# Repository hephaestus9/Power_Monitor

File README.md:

Power_Monitor
=============

Arduino and Processing sketches for Power Monitor Shield

*Boards v1r3 and v2r1 are not fully tested

This project is based on the work done by Christopher McNally.
Please view the Design_Report.pdf document for the write up of the project, and [website] (http://people.ece.cornell.edu/land/courses/eceprojectsland/STUDENTPROJ/2009to2010/csm44/index.html).

>The sample code was written for use with the 3000 Turn [CR Magnetics](http://www.crmagnetics.com/Products/CR3100-Series-P75.aspx) split core transformer. 

>If using the current transformer from [seeedstudio](http://www.seeedstudio.com/depot/Noninvasive-AC-Current-Sensor-100A-max-p-547.html?cPath=25_28) then the code needs to be changed, as this is a 2000 turn transformer.

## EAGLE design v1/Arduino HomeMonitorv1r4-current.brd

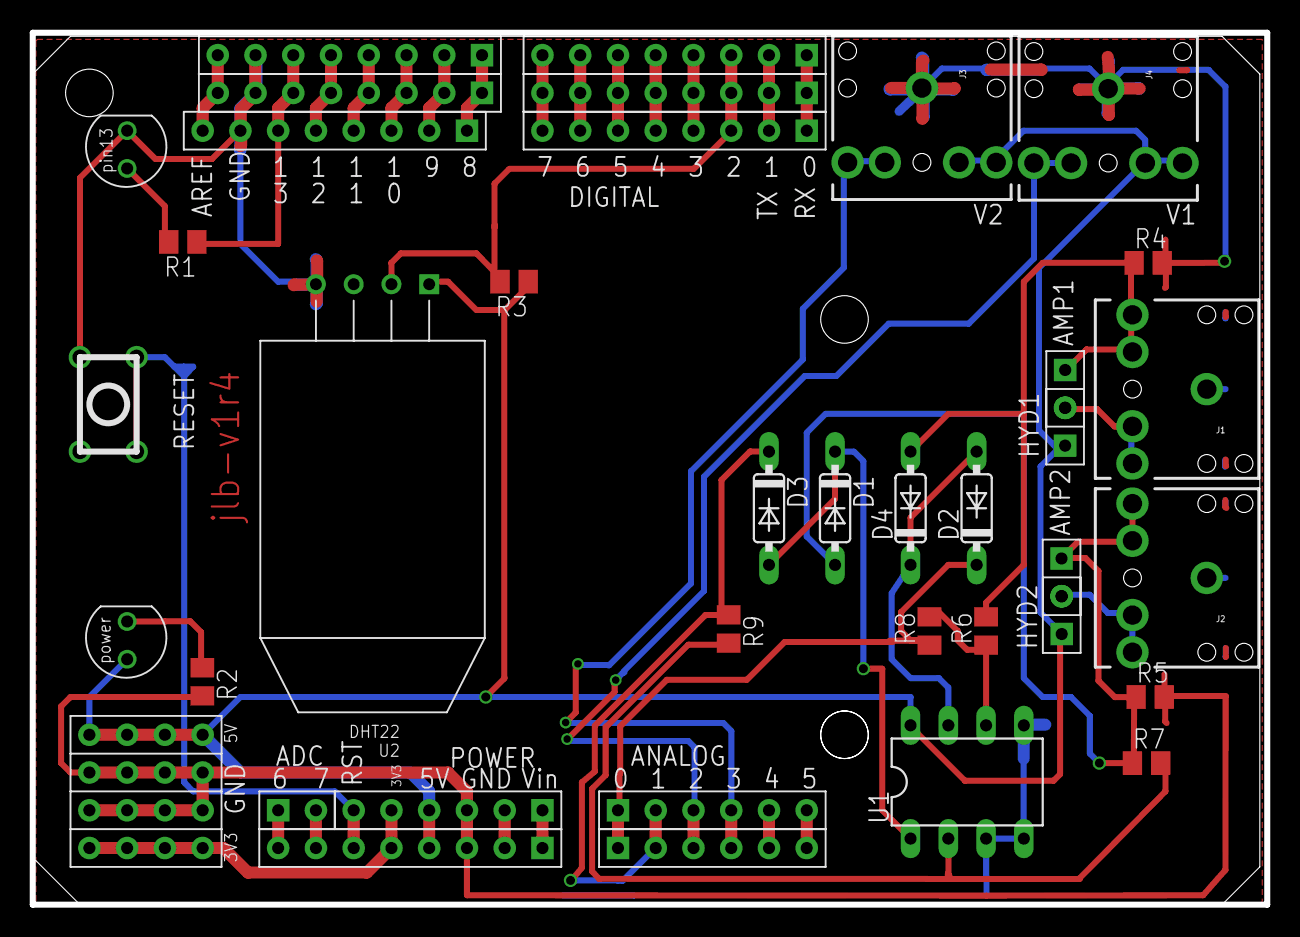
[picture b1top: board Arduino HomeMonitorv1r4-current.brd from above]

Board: 2 copper layers, 83.1 x 58.7 mm, 34 parts (0 on the bottom side), 30 nets.

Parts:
ADC6_1, ADC6_2, ADC6_3, ADC6_4, ADC6_7: CK_12; CK_1*2
D1, D2, D3, D4: DO35-7
J1, J2, J3, J4: AUDIO-JACK
PB, PB1, PB2: CK_1X8
PC, PC1: CK_1*6
PD, PD1, PD2, PD3: CK_1X8
POWER: CK_1*6
R1, R2, R3, R4, R5, R6, R7, R8, R9: M0805
U1: DIL08
U2: DHT22; AM2302

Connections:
3V3: PD3.5, POWER.5
5V: PD3.4, POWER.4, U1.8
GND: J1.SLEEVE, J2.SLEEVE, PB.7, PB1.7, PB2.7, PD3.2, PD3.3, POWER.2, POWER.3, U1.3, U1.4
RST: PD3.6, POWER.6
RX: PD.1, PD1.1, PD2.1
S$3: PC.4, PC1.4
S$4: PC.3, PC1.3
S$5: D2.A, D4.C, U1.7
S$15: D1.C, D3.A, U1.1
S$26: PC.1, PC1.1
S$30: PC.2, PC1.2
S$168: PB.6, PB1.6, PB2.6
S$171: PD3.1, POWER.1
S$174: ADC6_7.1, PD3.8
S$177: ADC6_7.2, PD3.7
S$179: PD.4, PD1.4, PD2.4
S$180: PD.3, PD1.3, PD2.3
S$181: PD.5, PD1.5, PD2.5
S$182: PD.6, PD1.6, PD2.6
S$183: PD.7, PD1.7, PD2.7
S$184: PD.8, PD1.8, PD2.8
S$185: PB.1, PB1.1, PB2.1
S$186: PB.2, PB1.2, PB2.2
S$187: PB.3, PB1.3, PB2.3
S$188: PB.4, PB1.4, PB2.4
S$189: PB.5, PB1.5, PB2.5
S$191: PB.8, PB1.8, PB2.8
SCL: PC.6, PC1.6
SDA: PC.5, PC1.5
TX: PD.2, PD1.2, PD2.2

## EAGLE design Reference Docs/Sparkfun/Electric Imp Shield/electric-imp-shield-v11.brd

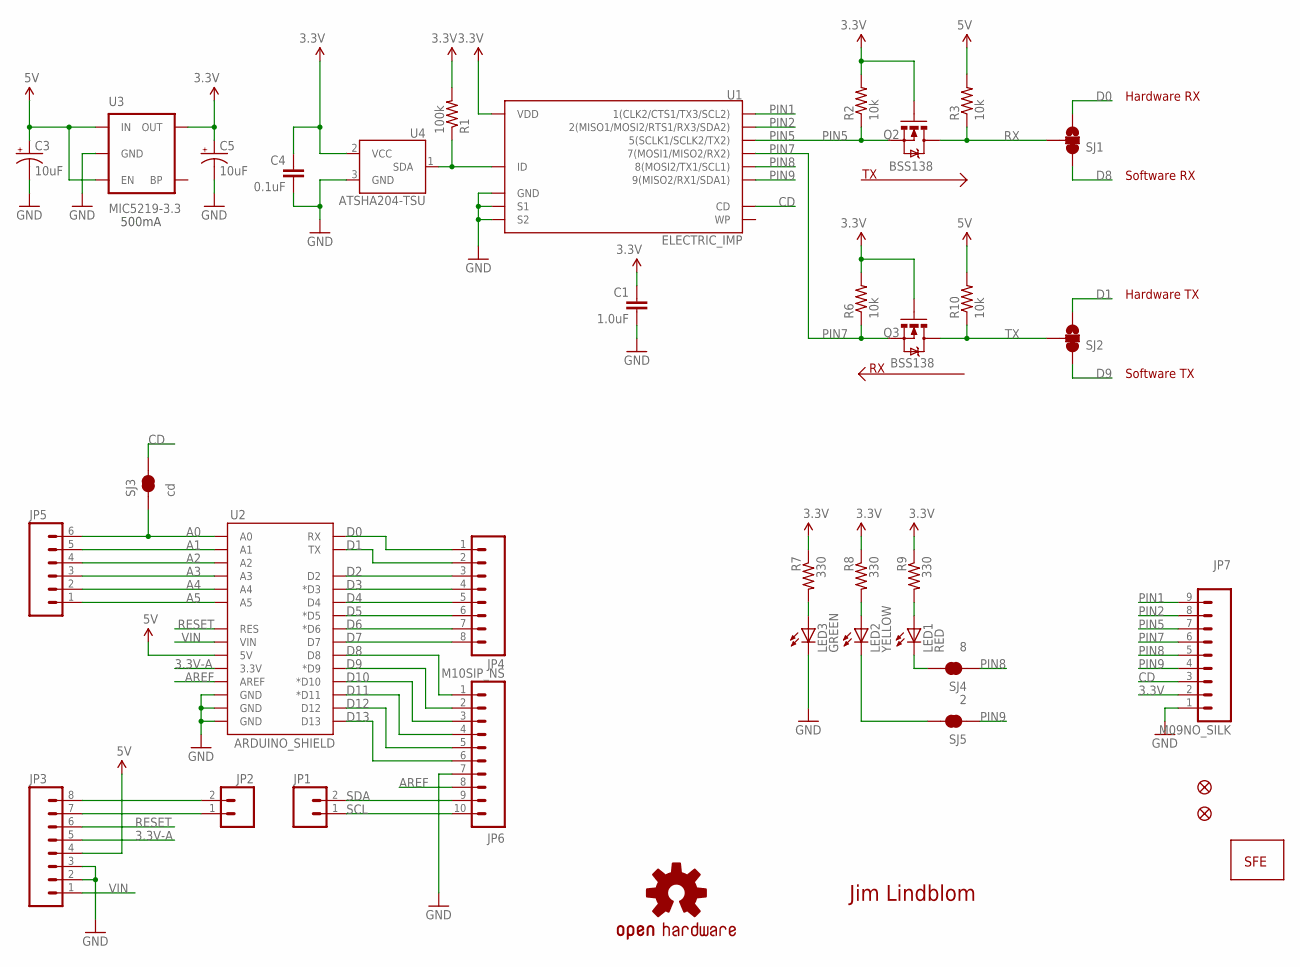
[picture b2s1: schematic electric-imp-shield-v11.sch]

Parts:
C1: 1.0uF; 0402-CAP
C3, C5: 10uF; EIA3216
C4: 0.1uF; 0402-CAP
JP1, JP2: M021X02_NO_SILK; 1X02_NO_SILK
JP3, JP4: M08SIP_NS; 1X08_NO_SILK
JP5: M06SIP_NS; 1X06_NO_SILK
JP6: M10SIP_NS; 1X10_NO_SILK
JP7: M09NO_SILK; 1X09_NO_SILK
JP8, JP9: FIDUCIALUFIDUCIAL; MICRO-FIDUCIAL
JP10: LOGO-SFENW2; SFE-NEW-WEB
LED1: RED; LED-0603
LED2: YELLOW; LED-0603
LED3: GREEN; LED-0603
Q2, Q3: BSS138; SOT23-3
R1: 100k; 0402-RES
R2, R3, R6, R10: 10k; 0402-RES
R7, R8, R9: 330; 0402-RES
SJ1, SJ2: SOLDERJUMPER_2WAYS; SJ_3
SJ3: cd; SJ_2S-TRACE
SJ4: 8; SJ_2S-TRACE
SJ5: 2; SJ_2S-TRACE
U1: ELECTRIC_IMP; SD_MMC_SOCKET
U2: ARDUINO_SHIELD; DUEMILANOVE_SHIELD_NOHOLES_NOLABELS
U3: MIC5219-3.3; SOT23-5
U4: ATSHA204-TSU; SOT23-3
U$7: OSHW-LOGOS; OSHW-LOGO-S

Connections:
3.3V: C1.1, C4.1, C5.A (+), JP7.2, Q2.1 (G), Q3.1 (G), R1.2, R2.2, R6.2, R7.1, R8.1, R9.1, U1.4 (VDD), U3.5 (OUT), U4.2 (VCC)
3.3V-A: JP3.5, U2.3.3V
5V: C3.A (+), JP3.4, R3.2, R10.2, U2.5V, U3.1 (IN), U3.3 (EN)
A0: JP5.6, SJ3.1, U2.A0
A1: JP5.5, U2.A1
A2: JP5.4, U2.A2
A3: JP5.3, U2.A3
A4: JP5.2, U2.A4
A5: JP5.1, U2.A5
ACTIVITY: LED1.C, SJ4.2
AREF: JP6.8, U2.AREF
CD: JP7.3, SJ3.2, U1.CD
D0: JP4.1, SJ1.3, U2.RX
D1: JP4.2, SJ2.3, U2.TX
D2: JP4.3, U2.D2
D3: JP4.4, U2.D3 (*D3)
D4: JP4.5, U2.D4
D5: JP4.6, U2.D5 (*D5)
D6: JP4.7, U2.D6 (*D6)
D7: JP4.8, U2.D7
D8: JP6.1, SJ1.1, U2.D8
D9: JP6.2, SJ2.1, U2.D9 (*D9)
D10: JP6.3, U2.D10 (*D10)
D11: JP6.4, U2.D11 (*D11)
D12: JP6.5, U2.D12
D13: JP6.6, U2.D13
GND: C1.2, C3.C (-), C4.2, C5.C (-), JP3.2, JP3.3, JP6.7, JP7.1, LED3.C, U1.3 (GND), U1.S1, U1.S2, U2.GND@0 (GND), U2.GND@1 (GND), U2.GND@2 (GND), U3.2 (GND), U4.3 (GND)
LINK: LED2.C, SJ5.2
unnamed: R1.1, U1.6 (ID), U4.1 (SDA)
unnamed: JP2.2, JP3.8
unnamed: JP2.1, JP3.7
unnamed: LED3.A, R7.2
unnamed: LED2.A, R8.2
unnamed: LED1.A, R9.2
PIN1: JP7.9, U1.1 (1(CLK2/CTS1/TX3/SCL2))
PIN2: JP7.8, U1.2 (2(MISO1/MOSI2/RTS1/RX3/SDA2))
PIN5: JP7.7, Q2.2 (S), R2.1, U1.5 (5(SCLK1/SCLK2/TX2))
PIN7: JP7.6, Q3.2 (S), R6.1, U1.7 (7(MOSI1/MISO2/RX2))
PIN8: JP7.5, SJ4.1, U1.8 (8(MOSI2/TX1/SCL1))
PIN9: JP7.4, SJ5.1, U1.9 (9(MISO2/RX1/SDA1))
RESET: JP3.6, U2.RES
RX: Q2.3 (D), R3.1, SJ1.2
SCL: JP1.1, JP6.10
SDA: JP1.2, JP6.9
TX: Q3.3 (D), R10.1, SJ2.2
VIN: JP3.1, U2.VIN

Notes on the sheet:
Hardware RX
Software RX
Hardware TX
Software TX
500mA
Jim Lindblom

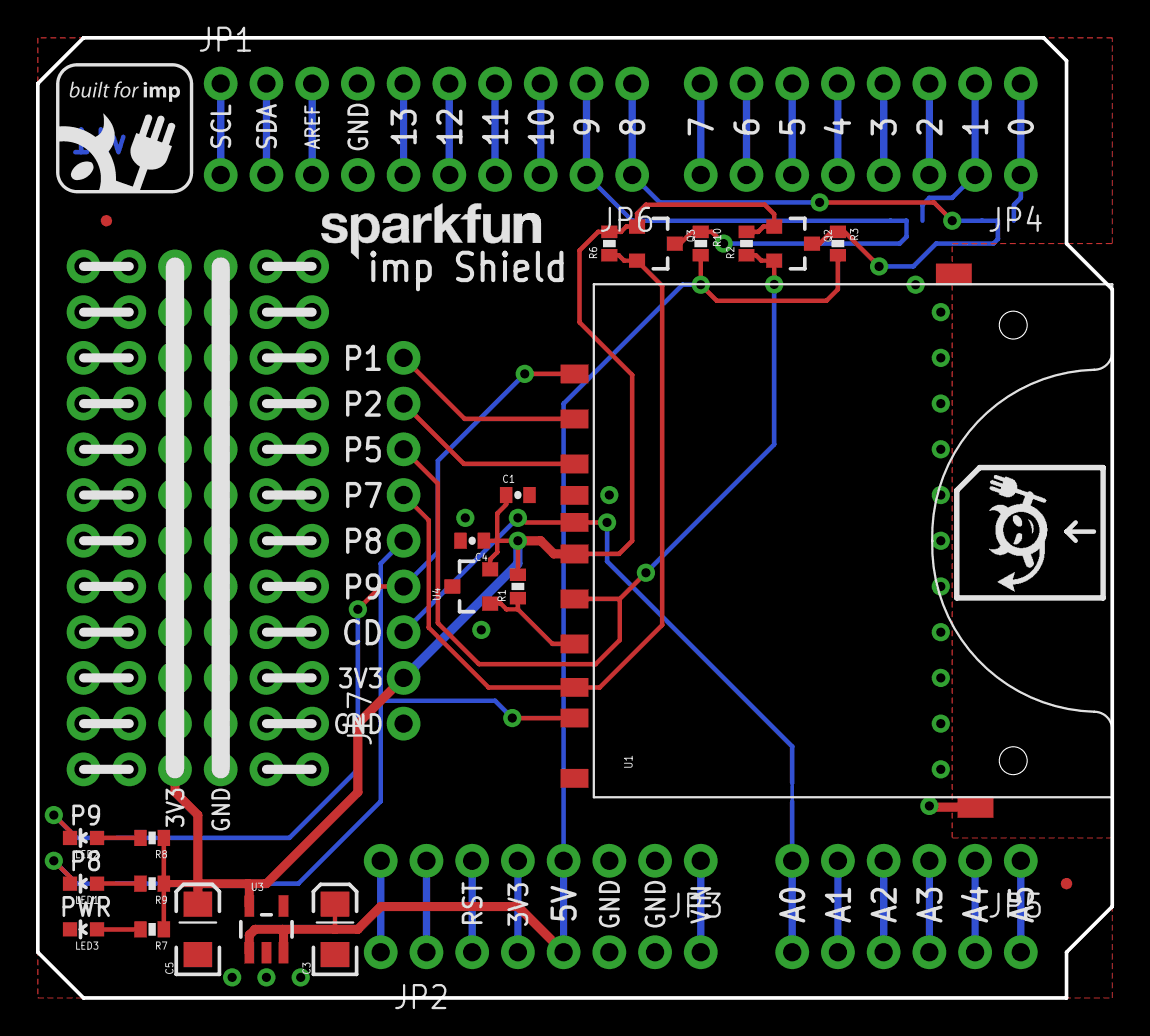
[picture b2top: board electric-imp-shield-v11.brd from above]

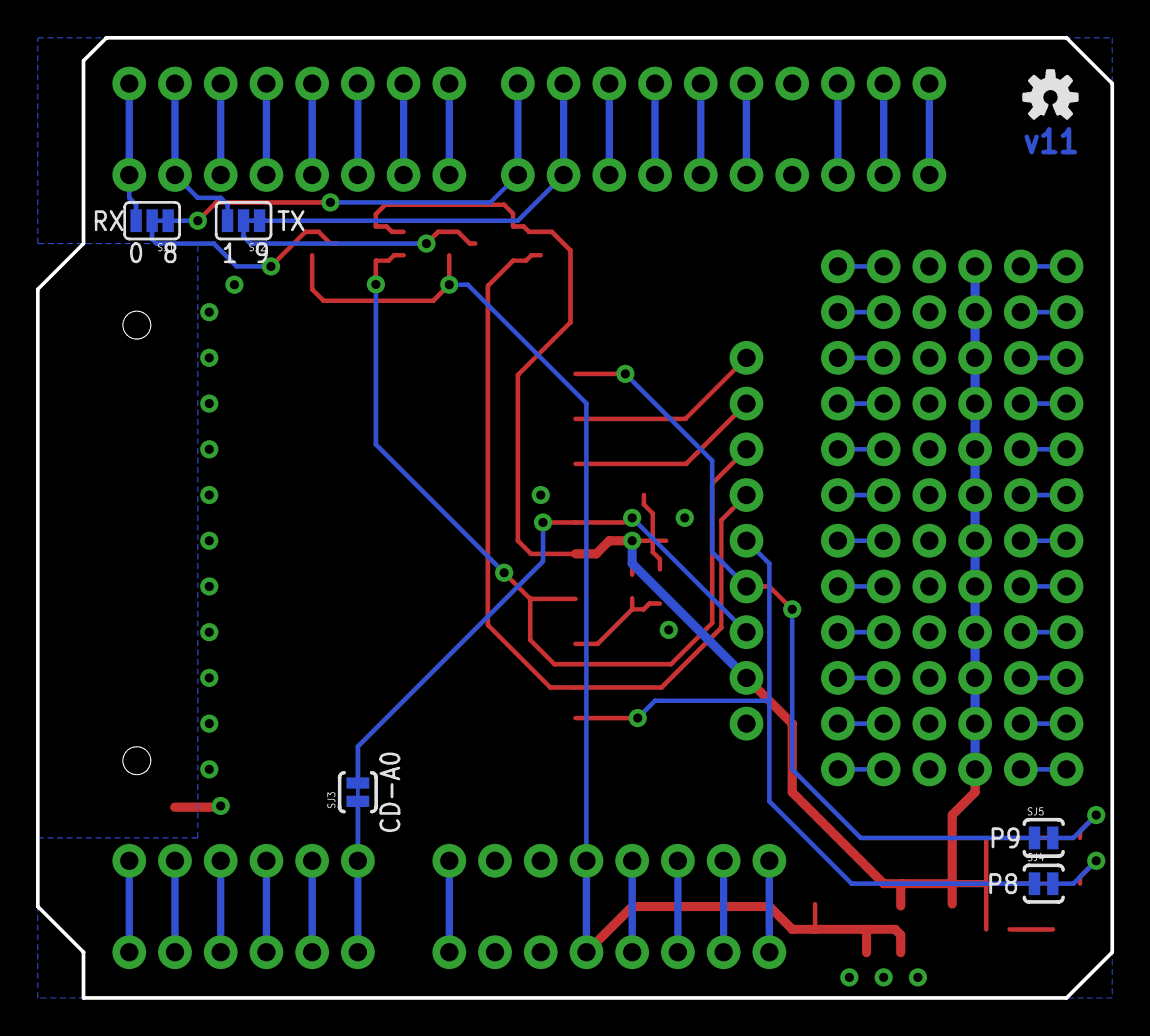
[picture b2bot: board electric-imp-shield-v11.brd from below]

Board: 2 copper layers, 59.7 x 53.3 mm, 37 parts (6 on the bottom side), 46 nets.

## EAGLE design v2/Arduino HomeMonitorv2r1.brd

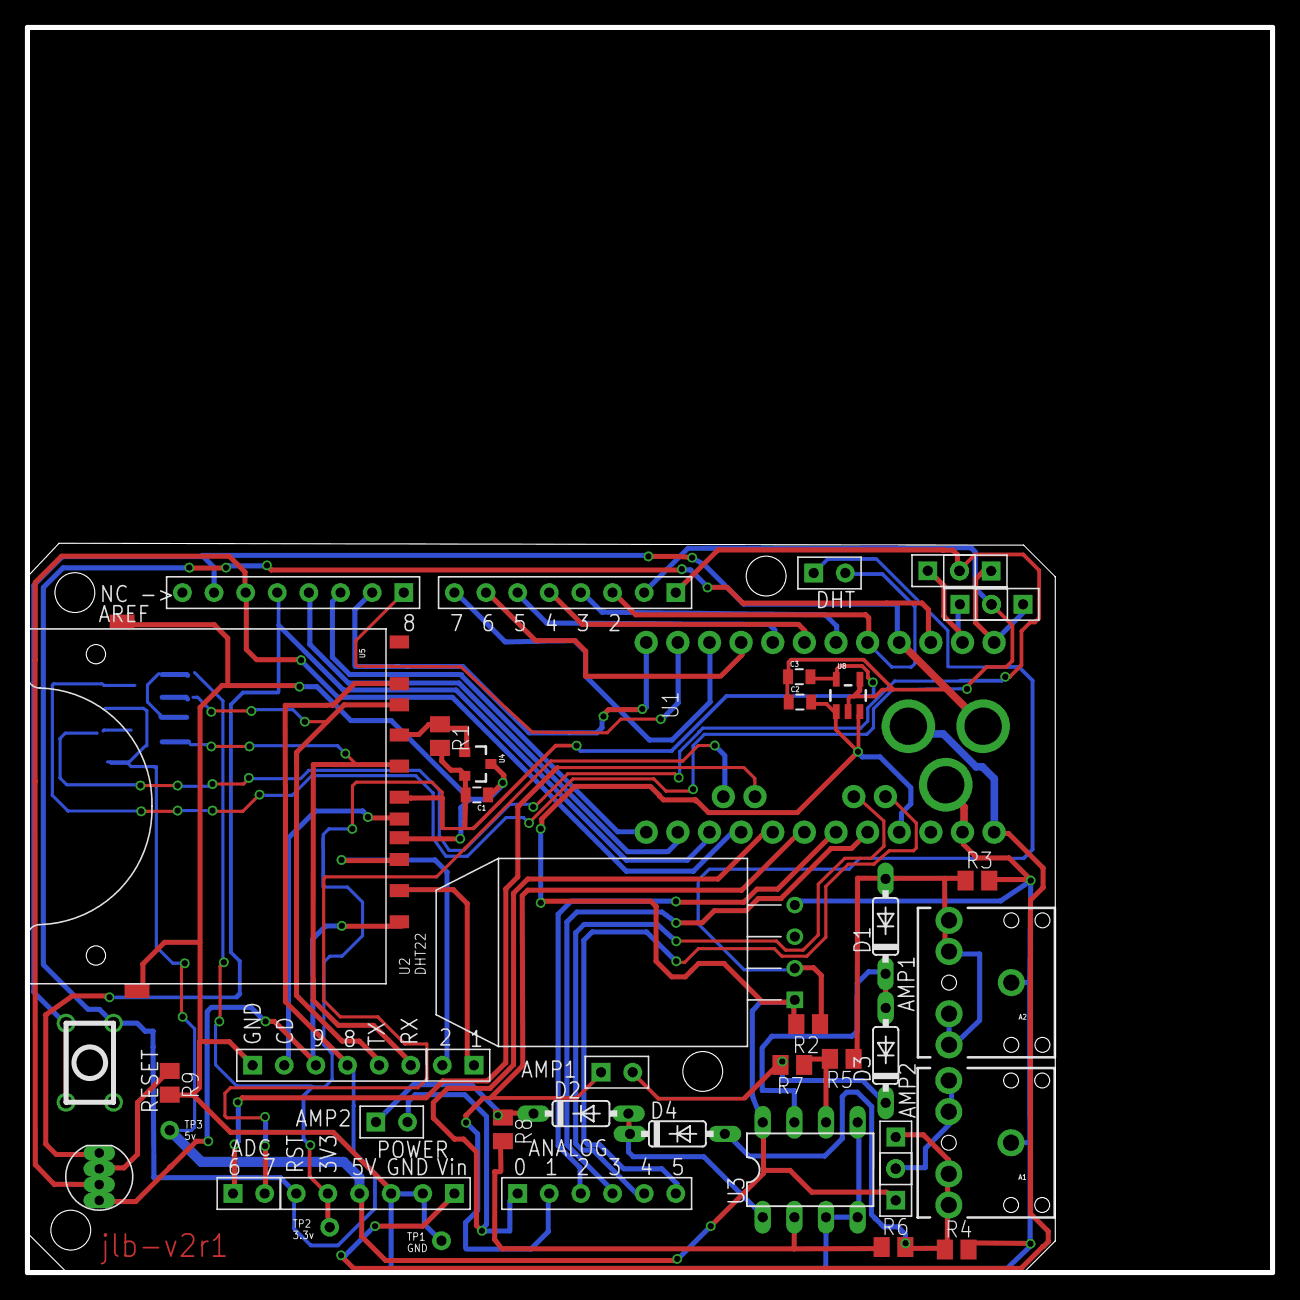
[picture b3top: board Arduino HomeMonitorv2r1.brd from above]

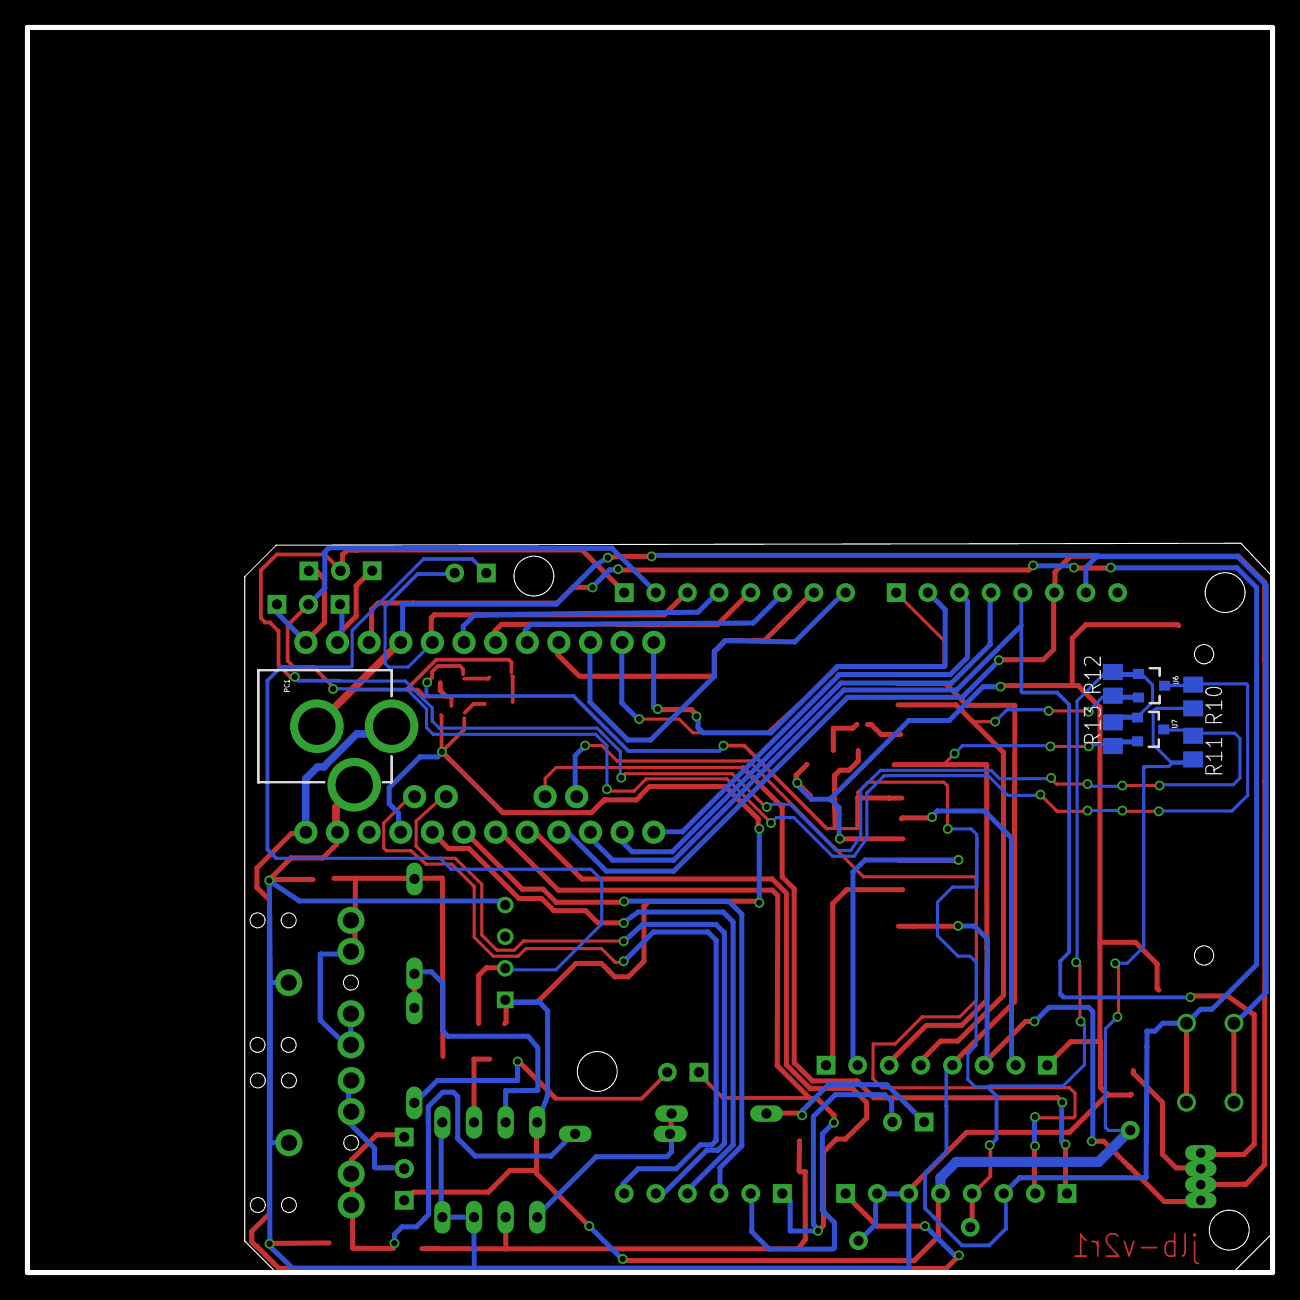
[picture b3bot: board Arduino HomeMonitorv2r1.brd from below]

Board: 2 copper layers, 100.0 x 100.0 mm, 48 parts (7 on the bottom side), 2 nets.

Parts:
A1, A2: AUDIO-JACK
ADC6_1, ADC6_2, ADC6_3, ADC6_4, ADC6_5, ADC6_6, ADC6_7, ADC6_8, ADC6_9, ADC6_10, ADC6_11: CK_12; CK_1*2
C1: 0.1uF; 0805
C2, C3: 10uF; 0805
D1, D2, D3, D4: DO35-7
E$1: LED-RGB-THRU
PB: CK_1X8
PC: CK_1*6
PC1: POWER_JACK_PTH
PD: CK_1X8
POWER, POWER1: CK_1*6
R1: 100k; M0805
R2, R3, R4, R5, R6, R7, R8, R9, R10, R11, R12, R13: M0805
U1: ARDUINO_PRO_MINI
U2: DHT22; AM2302
U3: DIL08
U4: ATSHA204-TSU; SOT23-3
U5: SD_MMC_SOCKET
U6: BSS138; SOT23-3
U7: SOT23-3
U8: MIC5219-3.3; SOT23-5

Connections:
---: U3.3, U3.4
S$263: A1.SLEEVE, A2.SLEEVE

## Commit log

2014-04-09 Example Files
2014-04-09 Source Document
2014-04-14 Board drawing
2014-04-15 board edit
2014-06-12 new board
2014-06-12 upload board
2014-06-12 Docs
2014-06-13 change board drawing
2014-06-13 Change v2 Board
    EI pin1 - arduino reset
    EI pin8 - LED
    EI pin9 - LED
2014-06-15 Add Electric Imp code and restructure files.
2014-06-15 Possible Sensor Boards
2014-07-06 Rev 4
2014-07-12 Rev 4
    Fixed some errors
2014-07-12 Copper Pour

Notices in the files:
parts and their libraries:
SparkFun-Boards: Licensing: CC v3.0 Share-Alike You are welcome to use this library for commercial purposes.
SparkFun-Aesthetics: Released under the Creative Commons
SparkFun-Aesthetics: http://creativecommons.org/licenses/by-sa/3.0
